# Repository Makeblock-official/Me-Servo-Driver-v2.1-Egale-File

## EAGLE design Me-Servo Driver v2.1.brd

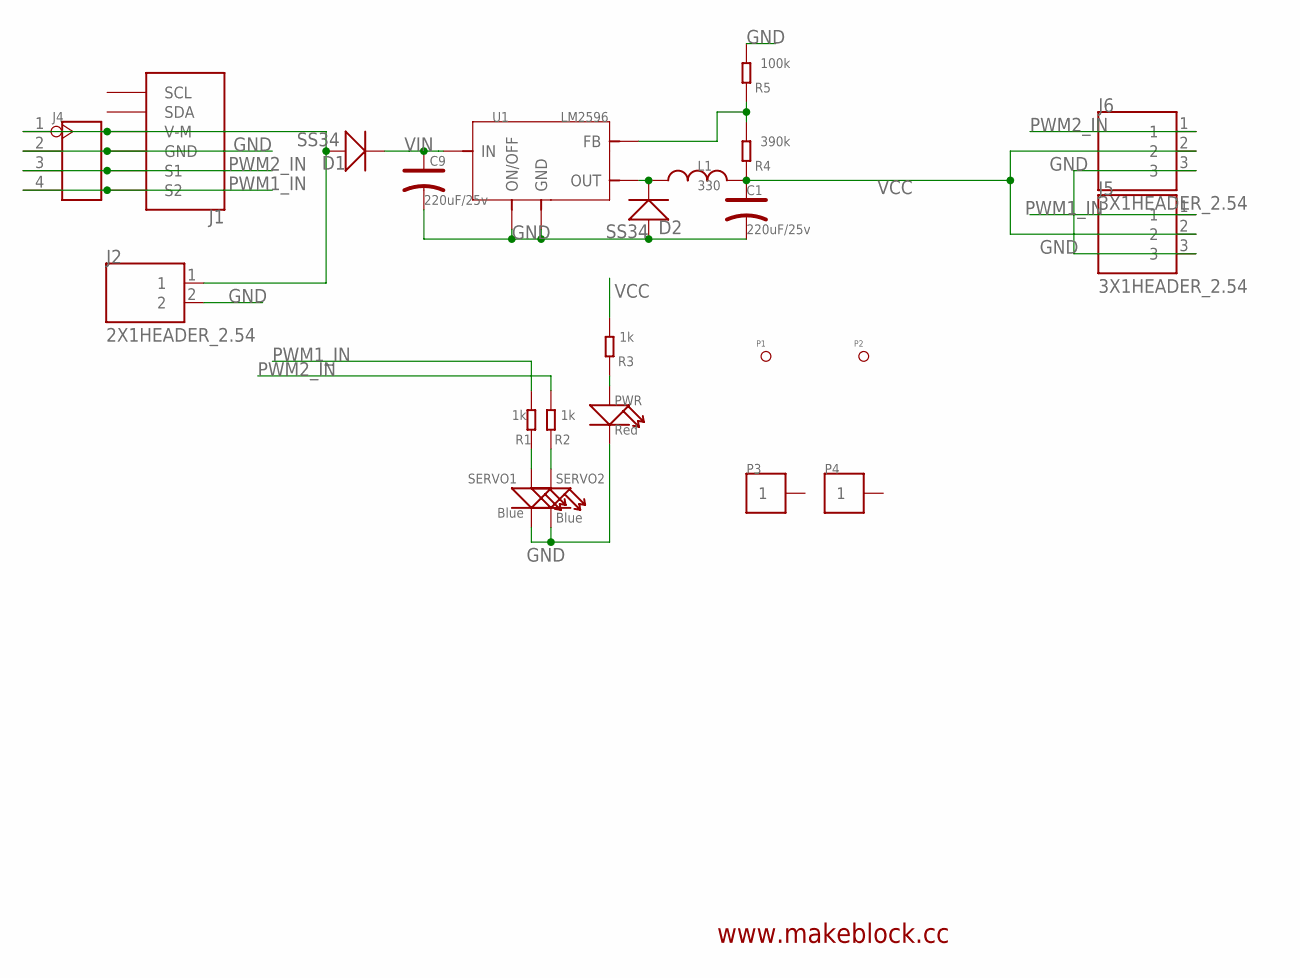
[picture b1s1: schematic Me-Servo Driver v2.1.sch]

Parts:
C1, C9: 220uF/25v; ELECTRO-SMD-E-7.8MM
D1, D2: SS34; D2010
J1: RJ11-6P6C-MOTOR; RJ11-6P6C
J2: 2X1HEADER_2.54
J4: HEADER-4P-60/35MIL; 4P-65/35MIL
J5, J6: 3X1HEADER_2.54
L1: 330; 12X12_INDUCTANCE
P1, P2: PAD-MARK; ROUND-MARK-1.0
P3, P4: PAD-1P-4MM; HOLE-01
PWR: Red; LED-0603
R1, R2, R3: 1k; 0603
R4: 390k; 0603
R5: 100k; 0603
SERVO1, SERVO2: Blue; LED-0603
U1: LM2596

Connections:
GND: C1.-, C9.-, D2.+, J1.4 (GND), J2.2, J4.2, J5.3, J6.3, PWR.-, R5.2, SERVO1.-, SERVO2.-, U1.3 (GND), U1.4 (GND), U1.6 (ON/OFF)
unnamed: D1.+, J1.3 (V-M), J2.1, J4.1
unnamed: PWR.+, R3.1
unnamed: R1.1, SERVO1.+
unnamed: R2.1, SERVO2.+
unnamed: D2.-, L1.P$1 (1), U1.2 (OUT)
unnamed: R4.2, R5.1, U1.5 (FB)
PWM1_IN: J1.6 (S2), J4.4, J5.1, R1.2
PWM2_IN: J1.5 (S1), J4.3, J6.1, R2.2
VCC: C1.+, J5.2, J6.2, L1.P$2 (2), R3.2, R4.1
VIN: C9.+, D1.-, U1.1 (IN)

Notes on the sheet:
www.makeblock.cc

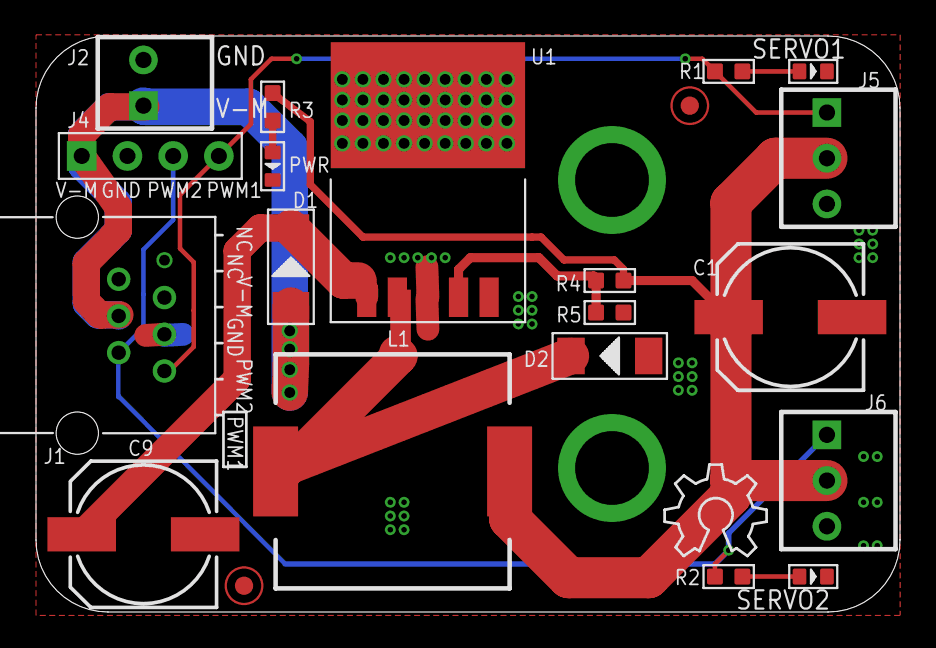
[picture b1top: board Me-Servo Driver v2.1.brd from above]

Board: 2 copper layers, 48.0 x 32.0 mm, 25 parts (1 on the bottom side), 11 nets.

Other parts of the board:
U$1: OSHW_6X200_NOTEXT
U$3: LOGO-3/2

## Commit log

2013-08-27 PCB files
